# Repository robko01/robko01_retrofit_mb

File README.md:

# Robko 01 retrofit main board

KiCad hardware design for the Robko 01 retrofit, with an ESP32 interface and six stepper-driver positions.

## Open the design

Open [robko01_retrofit_mb.kicad_pro](hardware/kicad/robko01_retrofit_mb.kicad_pro) in KiCad. The design was saved with KiCad 8; KiCad 9 is installed locally and can render it. The project uses the stable name `robko01_retrofit_mb`; revisions are recorded in Git.

## Repository layout

| Path | Contents |
| --- | --- |
| `hardware/kicad/` | Project, PCB, and schematic sources |
| `hardware/3dmodels/` | Board-local component models and their provenance |
| `docs/pinmap.md` | ESP32 pin mapping and discrepancies to review |
| `scripts/` | Repeatable local tools |
| `outputs/` | Generated renders, 3D exports, and manufacturing files; ignored by Git |

## Documentation

- [ESP32 pin mapping](docs/pinmap.md)
- [Board-local 3D models](hardware/3dmodels/README.md)
- [Repository working conventions](AGENTS.md)

## Render the board

From the repository root in PowerShell:

```powershell
powershell -NoProfile -ExecutionPolicy Bypass -File .\scripts\render-board.ps1
```

The command allows this local script to run for that PowerShell process without changing the system execution policy. Requires KiCad 9 or later; component models are included in this repository. The script finds KiCad on PATH or under Program Files. To select an installation:

```powershell
powershell -NoProfile -ExecutionPolicy Bypass -File .\scripts\render-board.ps1 -KiCadCli 'C:\Program Files\KiCad\9.0\bin\kicad-cli.exe'
```

The angled and top views are written to `outputs/renders/board-3d.png` and `outputs/renders/board-top.png`. The script uses an isolated configuration under `outputs/render-config/` to show both SMD and through-hole models while preserving personal KiCad settings. All 68 physical components have models; the 16 solder jumpers appear as PCB pads. See [model sources and approximations](hardware/3dmodels/README.md).

In KiCad's interactive 3D Viewer, enable **SMD Models** in the Appearance panel to show the diodes and surface-mount resistors and capacitors. The `S` shortcut toggles this visibility setting; it is saved in your local KiCad settings, separately from the board's model assignments. See the [KiCad 3D Viewer documentation](https://docs.kicad.org/9.0/en/pcbnew/pcbnew.html#_3d_viewer).

## Working conventions

Keep editable design sources and reviewed documentation in Git. Put generated exports and manufacturing outputs under `outputs/`. KiCad automatic backups, caches, and per-user settings are ignored. Use Git commits for design history instead of adding dated project folders.

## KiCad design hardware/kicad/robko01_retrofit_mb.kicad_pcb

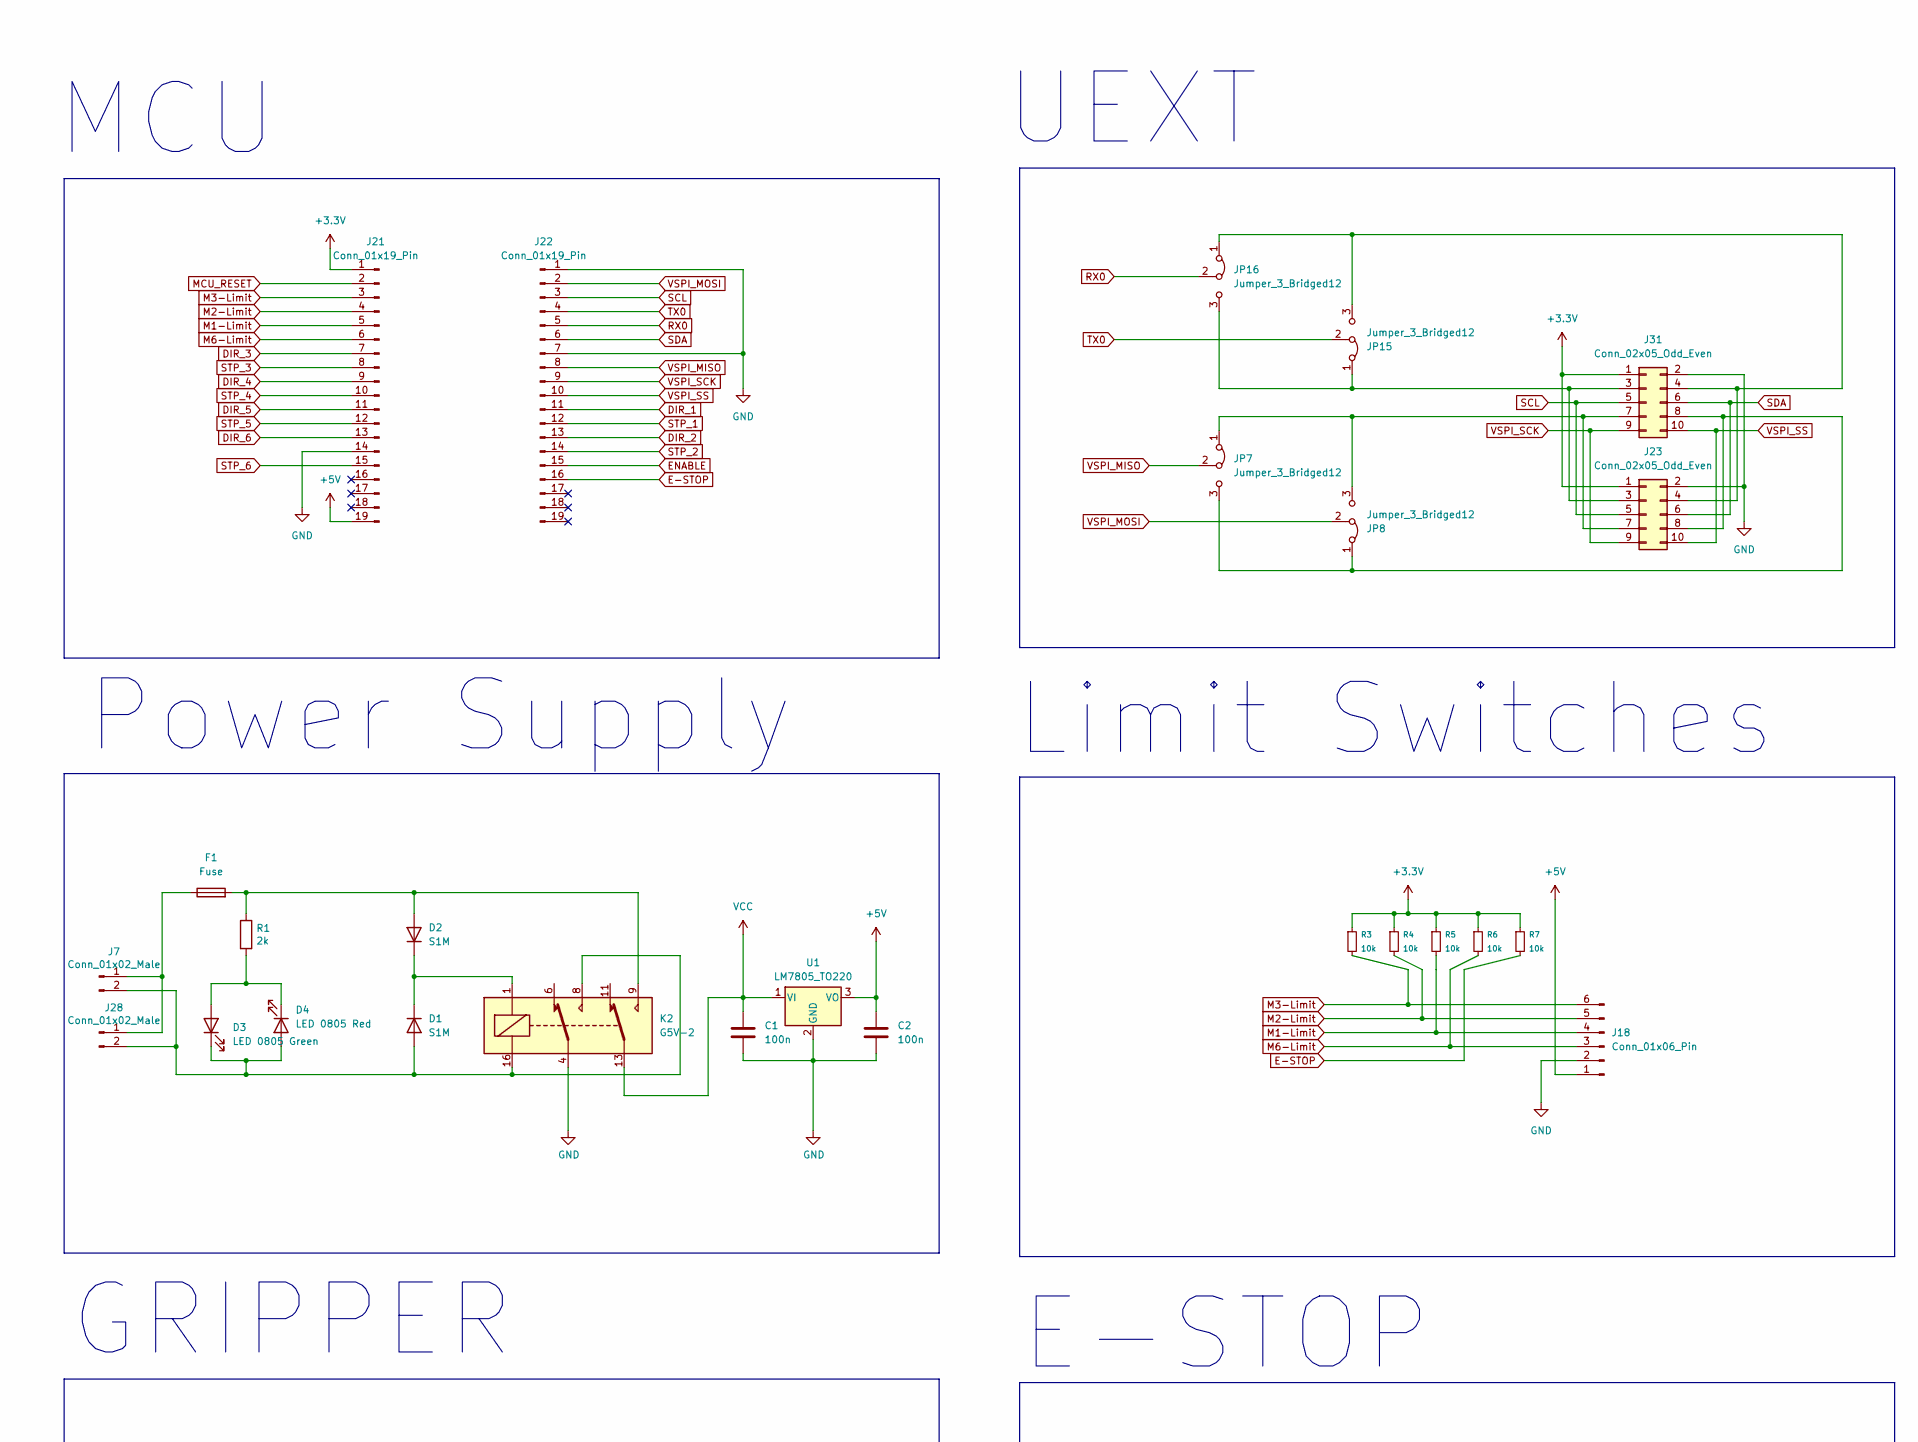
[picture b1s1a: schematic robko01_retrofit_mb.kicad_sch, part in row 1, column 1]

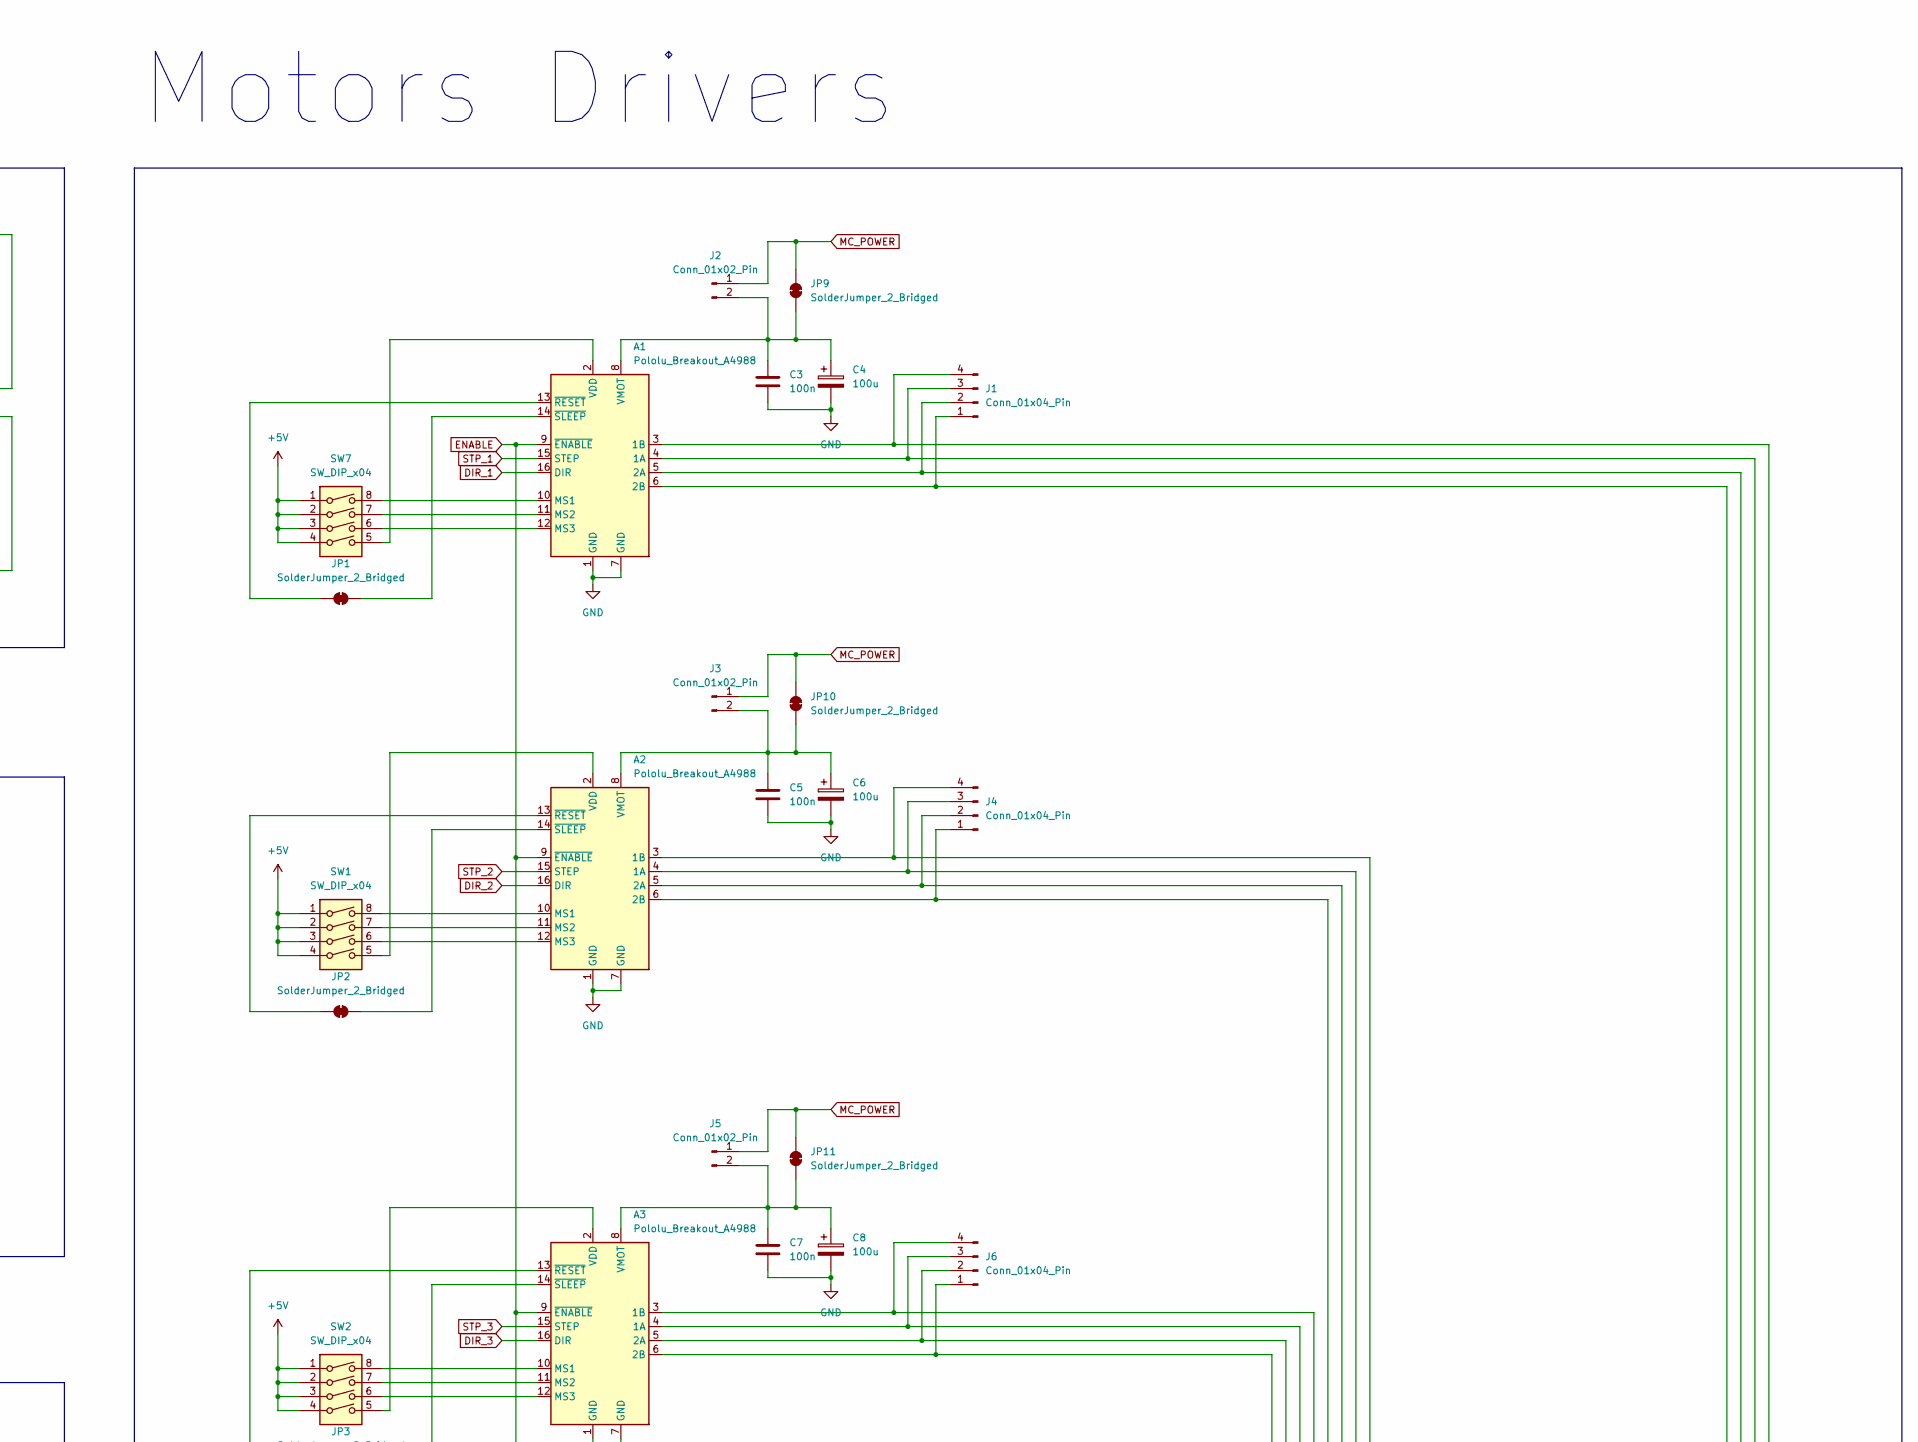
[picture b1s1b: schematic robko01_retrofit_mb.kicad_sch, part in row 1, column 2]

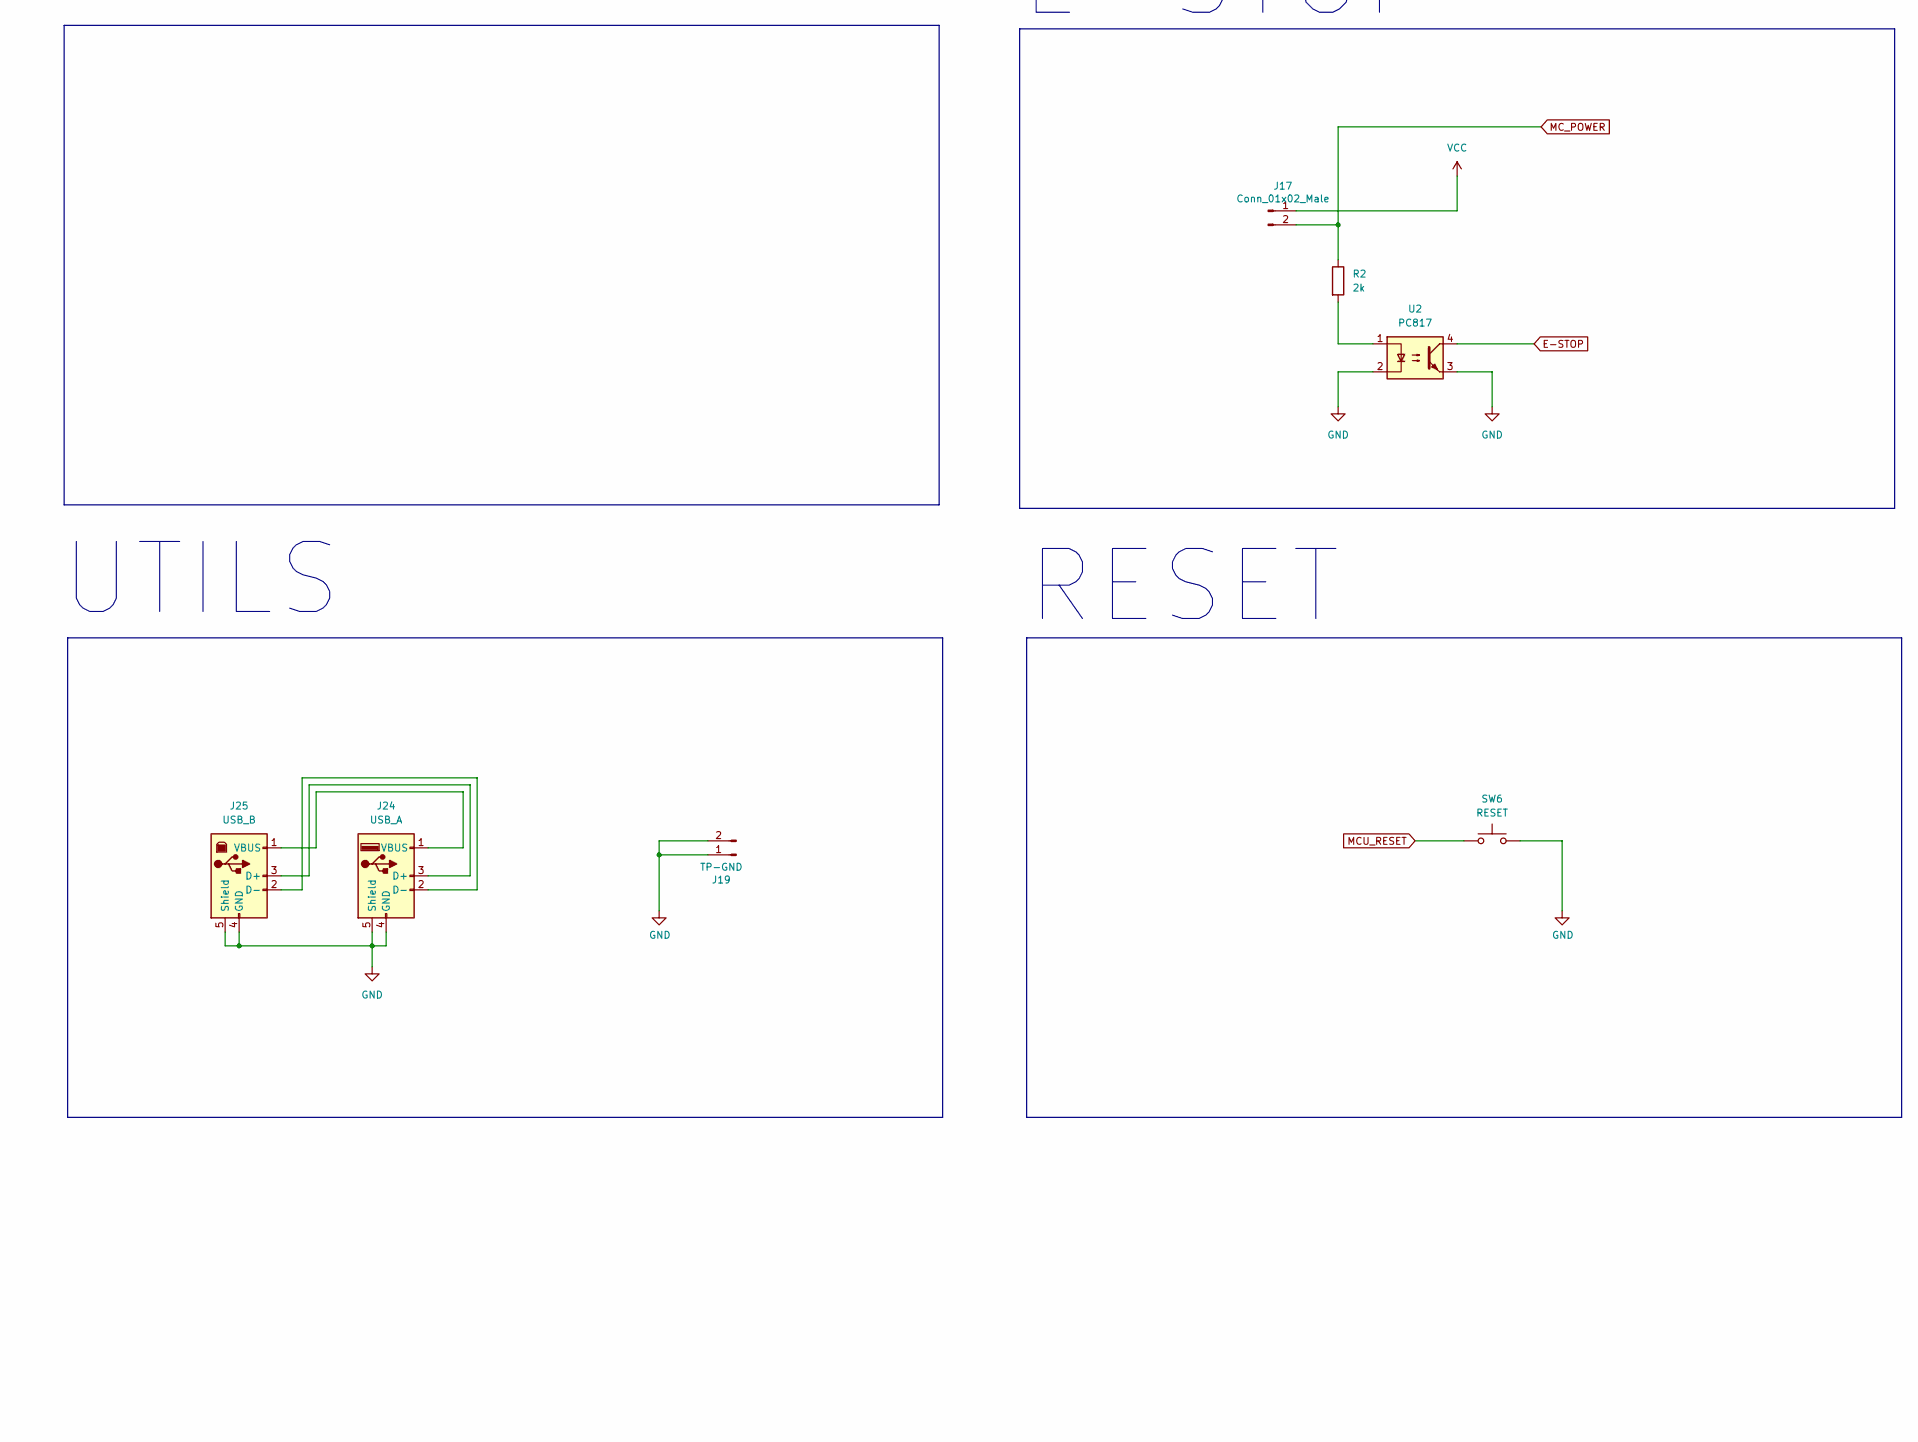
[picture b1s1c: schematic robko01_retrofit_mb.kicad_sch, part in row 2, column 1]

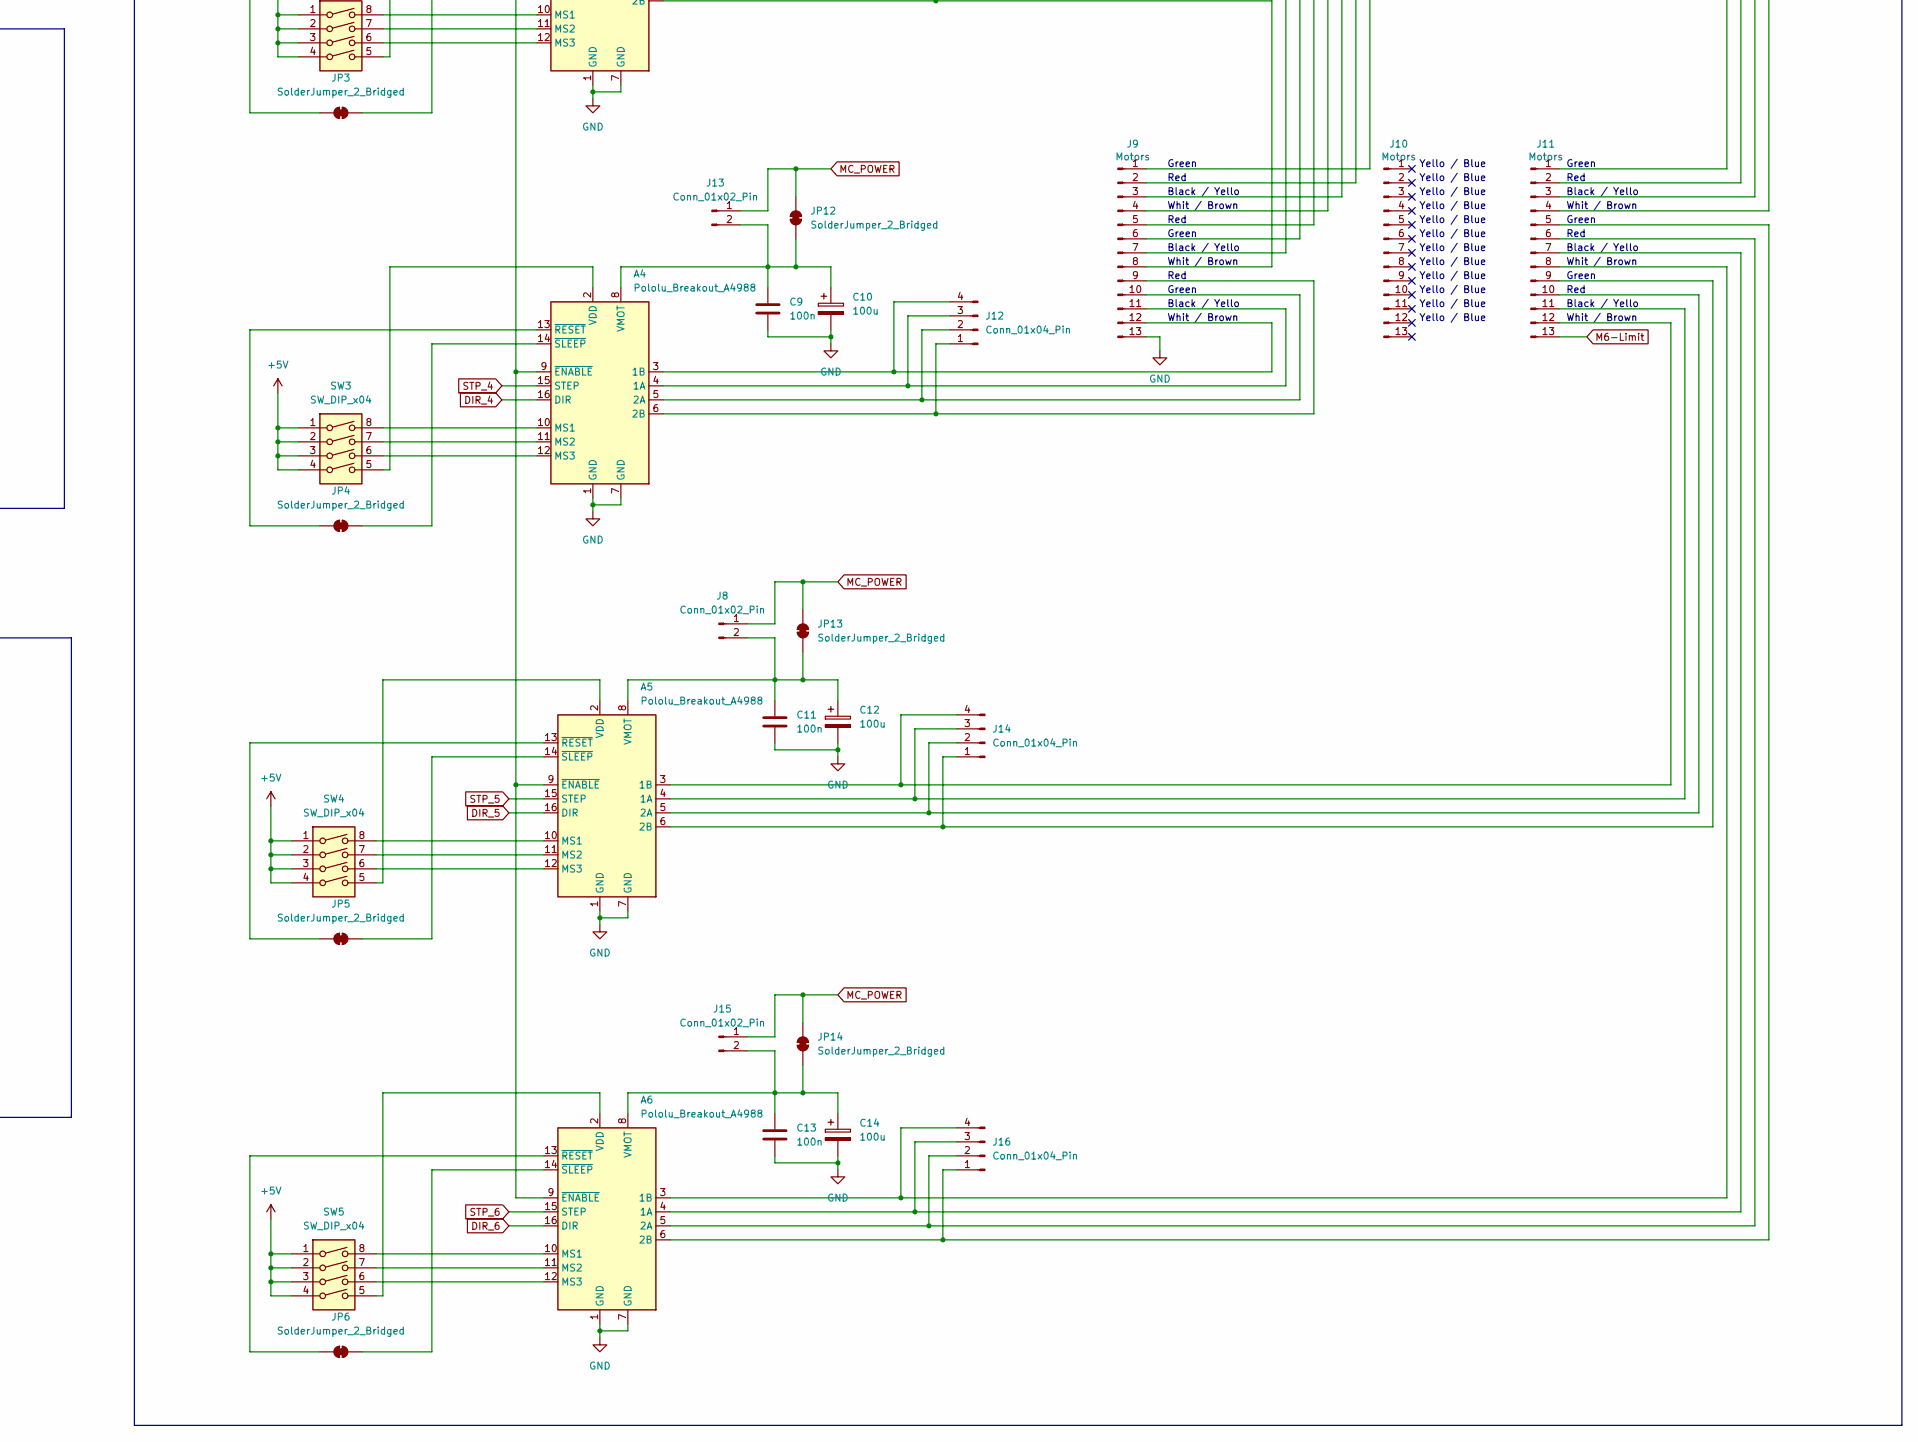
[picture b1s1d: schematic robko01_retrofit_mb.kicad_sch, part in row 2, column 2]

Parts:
A1, A2, A3, A4, A5, A6: Pololu_Breakout_A4988; Pololu_Breakout-16_15.2x20.3mm
C1, C2, C3, C5, C7, C9, C11, C13: 100n; C_0805_2012Metric
C4, C6, C8, C10, C12, C14: 100u; CP_Elec_8x10.5
D1, D2: S1M; D_SMA
D3: LED 0805 Green; LED_0805_2012Metric
D4: LED 0805 Red; LED_0805_2012Metric
F1: Fuse; Fuseholder_Clip-5x20mm_Bel_FC-203-22_Lateral_P17.80x5.00mm_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
J1, J4, J6, J12, J14, J16: Conn_01x04_Pin; PinHeader_1x04_P2.54mm_Horizontal
J2, J3, J5, J8, J13, J15: Conn_01x02_Pin; PinHeader_1x02_P2.54mm_Vertical
J7, J28: Conn_01x02_Male; PhoenixContact_MSTBA_2,5_2-G-5,08_1x02_P5.08mm_Horizontal
J9, J10, J11: Motors; PinHeader_1x13_P2.54mm_Vertical
J17: Conn_01x02_Male; PhoenixContact_MC_1,5_2-G-3.5_1x02_P3.50mm_Horizontal
J18: Conn_01x06_Pin; PinHeader_1x06_P2.54mm_Horizontal
J19: TP-GND; PinHeader_1x02_P2.54mm_Vertical
J21, J22: Conn_01x19_Pin; PinSocket_1x19_P2.54mm_Vertical
J23, J31: Conn_02x05_Odd_Even; IDC-Header_2x05_P2.54mm_Horizontal
J24: USB_A; USB_A_Molex_67643_Horizontal
J25: USB_B; USB_B_Lumberg_2411_02_Horizontal
JP1, JP2, JP3, JP4, JP5, JP6, JP9, JP10, JP11, JP12, JP13, JP14: SolderJumper_2_Bridged; SolderJumper-2_P1.3mm_Bridged2Bar_RoundedPad1.0x1.5mm
JP7, JP8, JP15, JP16: Jumper_3_Bridged12; SolderJumper-3_P1.3mm_Bridged2Bar12_Pad1.0x1.5mm
K2: G5V-2; Relay_DPDT_Omron_G5V-2
R1, R2: 2k; R_0805_2012Metric
R3, R4, R5, R6, R7: 10k; R_0805_2012Metric
SW1, SW2, SW3, SW4, SW5, SW7: SW_DIP_x04; DIP-8_W7.62mm
SW6: RESET; SW_Tactile_SPST_Angled_PTS645Vx39-2LFS
U1: LM7805_TO220; TO-220F-3_Horizontal_TabDown
U2: PC817; DIP-4_W7.62mm

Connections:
+3.3V: J21.1, J23.1, J31.1, R3.1, R4.1, R5.1, R6.1, R7.1
+5V: C2.1, J18.1, J21.19, SW1.1, SW1.2, SW1.3, SW1.4, SW2.1, SW2.2, SW2.3, SW2.4, SW3.1, SW3.2, SW3.3, SW3.4, SW4.1, SW4.2, SW4.3, SW4.4, SW5.1, SW5.2, SW5.3, SW5.4, SW7.1, SW7.2, SW7.3, SW7.4, U1.3 (VO)
DIR_1: A1.16 (DIR), J22.11
DIR_2: A2.16 (DIR), J22.13
DIR_3: A3.16 (DIR), J21.7
DIR_4: A4.16 (DIR), J21.9
DIR_5: A5.16 (DIR), J21.11
DIR_6: A6.16 (DIR), J21.13
E-STOP: J22.16, R7.2, U2.4
ENABLE: A1.9 (~ENABLE), A2.9 (~ENABLE), A3.9 (~ENABLE), A4.9 (~ENABLE), A5.9 (~ENABLE), A6.9 (~ENABLE), J22.15
GND: A1.1 (GND), A1.7 (GND), A2.1 (GND), A2.7 (GND), A3.1 (GND), A3.7 (GND), A4.1 (GND), A4.7 (GND), A5.1 (GND), A5.7 (GND), A6.1 (GND), A6.7 (GND), C1.2, C2.2, C3.2, C4.2, C5.2, C6.2, C7.2, C8.2, C9.2, C10.2, C11.2, C12.2, C13.2, C14.2, J9.13, J18.2, J19.1, J19.2, J21.14, J22.1, J22.7, J23.2, J24.4 (GND), J24.5 (Shield), J25.4 (GND), J25.5 (Shield), J31.2, K2.4, SW6.2, U1.2 (GND), U2.2, U2.3
M1-Limit: J18.4, J21.5, R5.2
M2-Limit: J18.5, J21.4, R4.2
M3-Limit: J18.6, J21.3, R3.2
M6-Limit: J11.13, J18.3, J21.6, R6.2
MCU_RESET: J21.2, SW6.1
MC_POWER: J2.1, J3.1, J5.1, J8.1, J13.1, J15.1, J17.2, JP9.1 (A), JP10.1 (A), JP11.1 (A), JP12.1 (A), JP13.1 (A), JP14.1 (A), R2.1
unnamed: A1.4 (1A), J1.3, J11.3
unnamed: A1.3 (1B), J1.4, J11.4
unnamed: A1.5 (2A), J1.2, J11.2
unnamed: A1.6 (2B), J1.1, J11.1
unnamed: A1.10 (MS1), SW7.8
unnamed: A1.11 (MS2), SW7.7
unnamed: A1.12 (MS3), SW7.6
unnamed: A1.2 (VDD), SW7.5
unnamed: A1.8 (VMOT), C3.1, C4.1, J2.2, JP9.2 (B)
unnamed: A1.13 (~RESET), JP1.1 (A)
unnamed: A1.14 (~SLEEP), JP1.2 (B)
unnamed: A2.4 (1A), J4.3, J9.2
unnamed: A2.3 (1B), J4.4, J9.1
unnamed: A2.5 (2A), J4.2, J9.3
unnamed: A2.6 (2B), J4.1, J9.4
unnamed: A2.10 (MS1), SW1.8
unnamed: A2.11 (MS2), SW1.7
unnamed: A2.12 (MS3), SW1.6
unnamed: A2.2 (VDD), SW1.5
unnamed: A2.8 (VMOT), C5.1, C6.1, J3.2, JP10.2 (B)
unnamed: A2.13 (~RESET), JP2.1 (A)
unnamed: A2.14 (~SLEEP), JP2.2 (B)
unnamed: A3.4 (1A), J6.3, J9.6
unnamed: A3.3 (1B), J6.4, J9.5
unnamed: A3.5 (2A), J6.2, J9.7
unnamed: A3.6 (2B), J6.1, J9.8
unnamed: A3.10 (MS1), SW2.8
unnamed: A3.11 (MS2), SW2.7
unnamed: A3.12 (MS3), SW2.6
unnamed: A3.2 (VDD), SW2.5
unnamed: A3.8 (VMOT), C7.1, C8.1, J5.2, JP11.2 (B)
unnamed: A3.13 (~RESET), JP3.1 (A)
unnamed: A3.14 (~SLEEP), JP3.2 (B)
unnamed: A4.4 (1A), J9.11, J12.3
unnamed: A4.3 (1B), J9.12, J12.4
unnamed: A4.5 (2A), J9.10, J12.2
unnamed: A4.6 (2B), J9.9, J12.1
unnamed: A4.10 (MS1), SW3.8
unnamed: A4.11 (MS2), SW3.7
unnamed: A4.12 (MS3), SW3.6
unnamed: A4.2 (VDD), SW3.5
unnamed: A4.8 (VMOT), C9.1, C10.1, J13.2, JP12.2 (B)
unnamed: A4.13 (~RESET), JP4.1 (A)
unnamed: A4.14 (~SLEEP), JP4.2 (B)
unnamed: A5.4 (1A), J11.11, J14.3
unnamed: A5.3 (1B), J11.12, J14.4
unnamed: A5.5 (2A), J11.10, J14.2
unnamed: A5.6 (2B), J11.9, J14.1
unnamed: A5.10 (MS1), SW4.8
unnamed: A5.11 (MS2), SW4.7
unnamed: A5.12 (MS3), SW4.6
unnamed: A5.2 (VDD), SW4.5
unnamed: A5.8 (VMOT), C11.1, C12.1, J8.2, JP13.2 (B)
unnamed: A5.13 (~RESET), JP5.1 (A)
unnamed: A5.14 (~SLEEP), JP5.2 (B)
unnamed: A6.4 (1A), J11.7, J16.3
unnamed: A6.3 (1B), J11.8, J16.4
unnamed: A6.5 (2A), J11.6, J16.2
unnamed: A6.6 (2B), J11.5, J16.1
unnamed: A6.10 (MS1), SW5.8
unnamed: A6.11 (MS2), SW5.7
unnamed: A6.12 (MS3), SW5.6
unnamed: A6.2 (VDD), SW5.5
unnamed: A6.8 (VMOT), C13.1, C14.1, J15.2, JP14.2 (B)
unnamed: A6.13 (~RESET), JP6.1 (A)
unnamed: A6.14 (~SLEEP), JP6.2 (B)
unnamed: D1.2 (A), D3.1 (K), D4.2 (A), J7.2, J28.2, K2.8, K2.16
unnamed: D1.1 (K), D2.1 (K), K2.1
unnamed: D2.2 (A), F1.2, K2.9, R1.1
unnamed: D3.2 (A), D4.1 (K), R1.2
unnamed: J23.3, J31.3, JP15.1 (A), JP16.3 (B)
unnamed: J23.4, J31.4, JP15.3 (B), JP16.1 (A)
unnamed: J23.7, J31.7, JP7.1 (A), JP8.3 (B)
unnamed: J23.8, J31.8, JP7.3 (B), JP8.1 (A)
unnamed: J24.3 (D+), J25.3 (D+)
unnamed: J24.2 (D-), J25.2 (D-)
unnamed: J24.1 (VBUS), J25.1 (VBUS)
unnamed: F1.1, J7.1, J28.1
unnamed: R2.2, U2.1
RX0: J22.5, JP16.2 (C)
SCL: J22.3, J23.5, J31.5
SDA: J22.6, J23.6, J31.6
STP_1: A1.15 (STEP), J22.12
STP_2: A2.15 (STEP), J22.14
STP_3: A3.15 (STEP), J21.8
STP_4: A4.15 (STEP), J21.10
STP_5: A5.15 (STEP), J21.12
STP_6: A6.15 (STEP), J21.15
TX0: J22.4, JP15.2 (C)
VCC: C1.1, J17.1, K2.13, U1.1 (VI)
VSPI_MISO: J22.8, JP7.2 (C)
VSPI_MOSI: J22.2, JP8.2 (C)
VSPI_SCK: J22.9, J23.9, J31.9
VSPI_SS: J22.10, J23.10, J31.10

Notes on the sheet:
Yello / Blue
Limit Switches
MCU
Black / Yello
Motors Drivers
Red
Whit / Brown
UTILS
Green
RESET
Power Supply
E-STOP
GRIPPER
UEXT

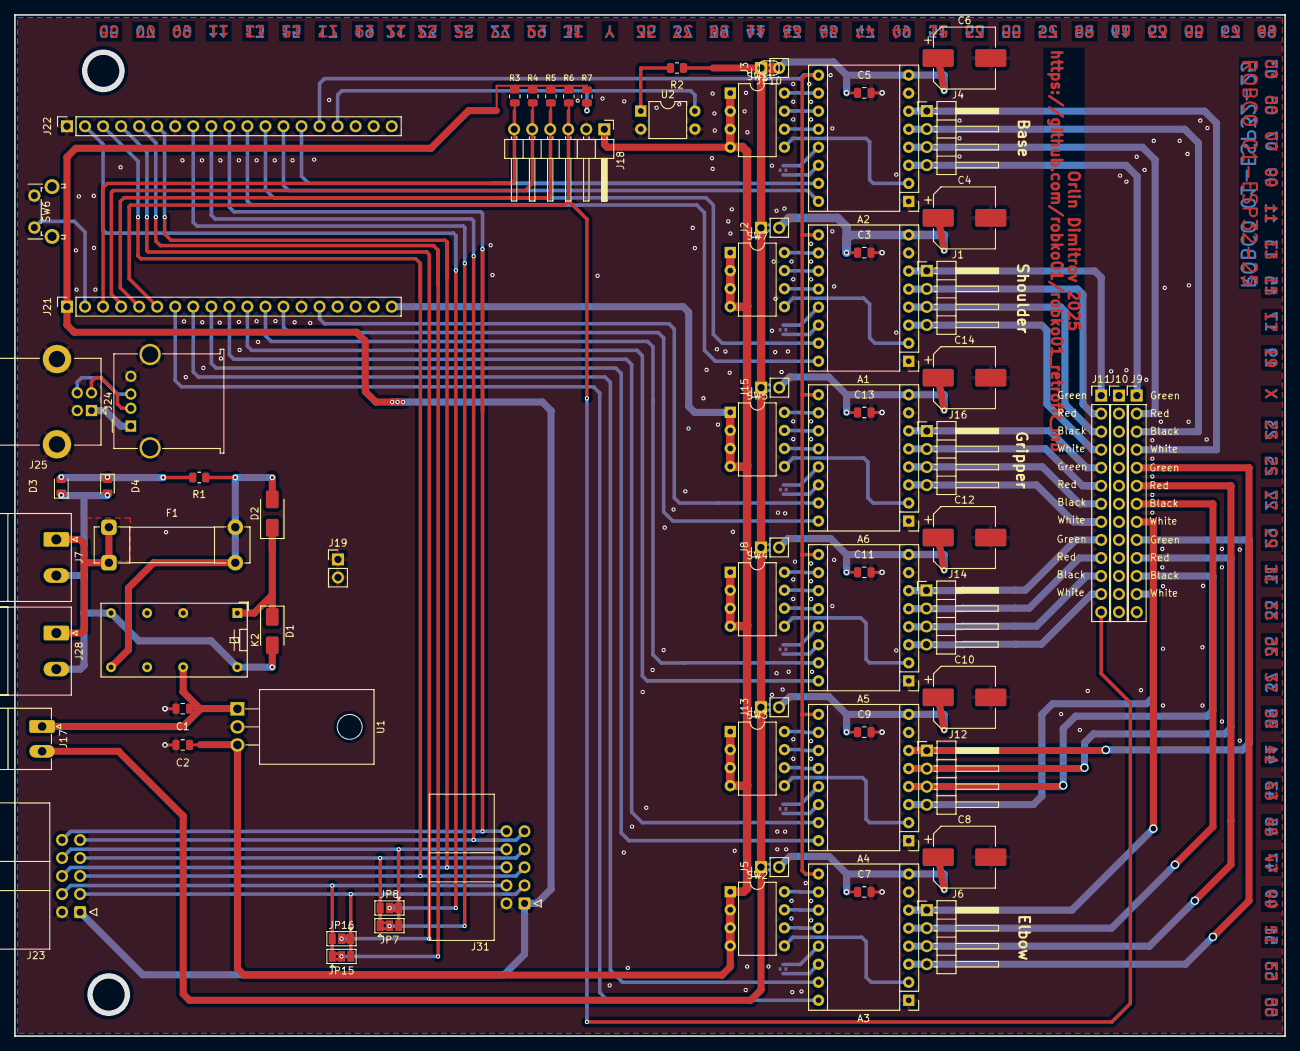
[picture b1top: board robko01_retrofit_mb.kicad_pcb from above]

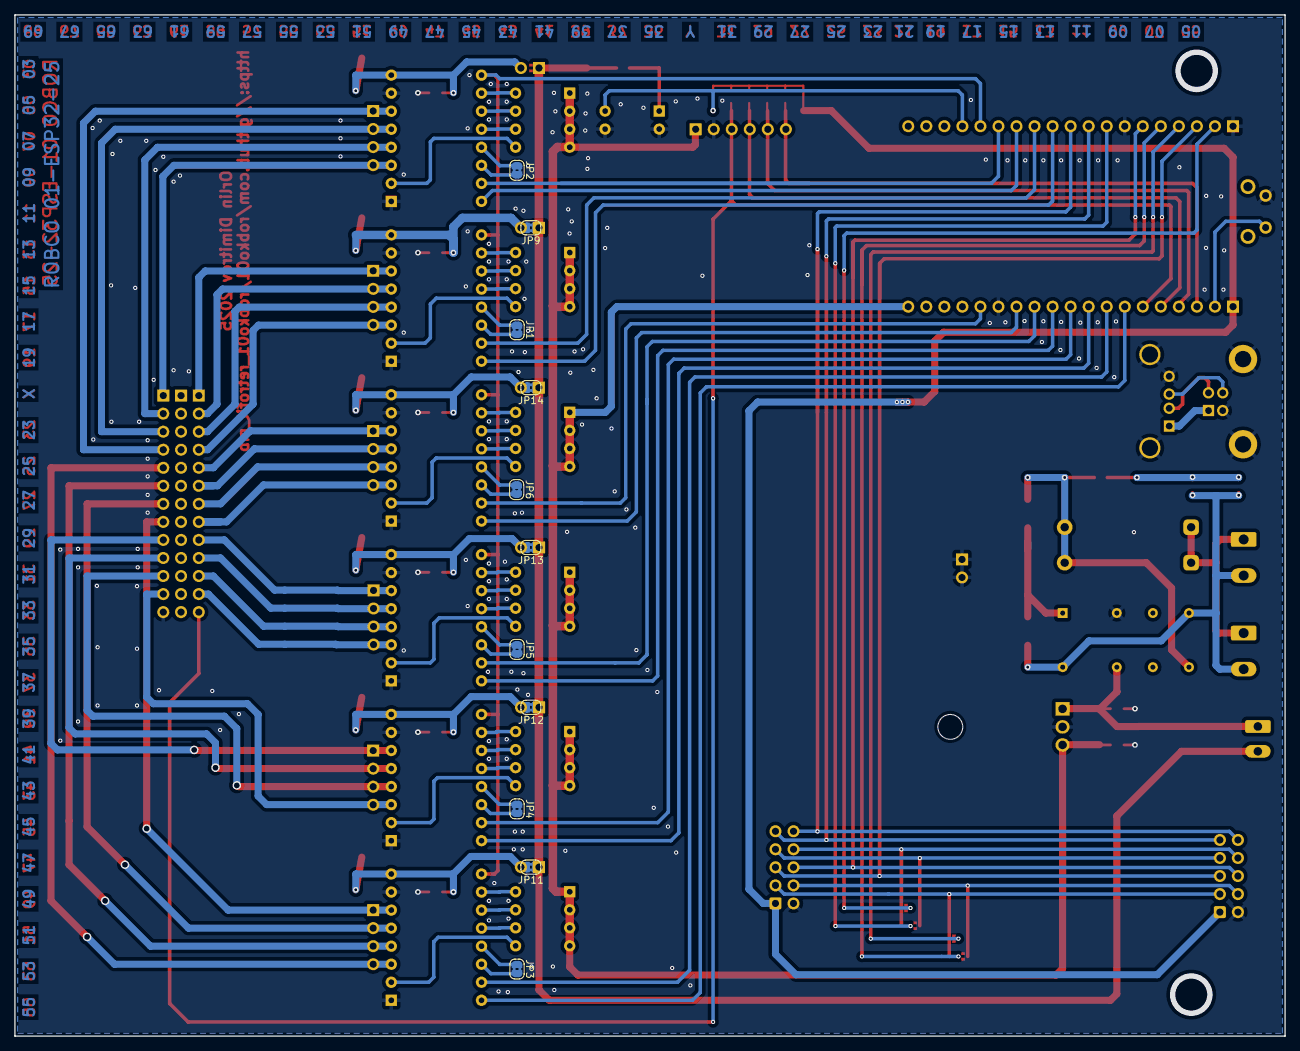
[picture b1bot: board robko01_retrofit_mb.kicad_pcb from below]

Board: 2 copper layers, 178.8 x 143.8 mm, 84 parts (11 on the bottom side), 111 nets.

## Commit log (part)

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2024-10-11 Fix main MCU footprint size
2024-11-08 Add pin mapping
2024-11-08 Fix geometry
2024-11-08 Fix pin mapping
2024-11-09 Relocate elements and fix power connector positions
2024-11-17 Add BOM
2024-12-12 Fix pinout
2024-12-17 Add small improvements
2024-12-18 Add more improvements
2025-01-11 Add E-Stop
2025-01-20 Add reset button and E-Stop
2025-01-21 Add E-Stop definition
2025-01-24 Add UEXT
2025-01-26 Add direction jumpers to UEXT
2025-01-27 Change jumpers for UEXT
2025-02-03 Add USB
2025-02-12 Update USB imp balance
2025-04-30 Change E-Stop connector, add default jumper to power supply of the stepper drivers, wireup limit switch of the gripper, rewire E-Stop sensor
